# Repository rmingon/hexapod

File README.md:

# Hexapod project

# ON HER LEGS

### Circuit schema with 18 servos connectors.

### PCB View

### 3D View

#### Info
In my hexapod project, i will create a specific pcb with ESP32 for online 
control.

All mcu are connected with I2C bus.

TODO
- [x] Add PCA9685-16 for control servos
- [x] add esp32 
- [x] add MCP9250
- [x] send pcb to JLCPCB
- [x] add lipo 2s charger
- [ ] change esp32 by a k210 kendryte

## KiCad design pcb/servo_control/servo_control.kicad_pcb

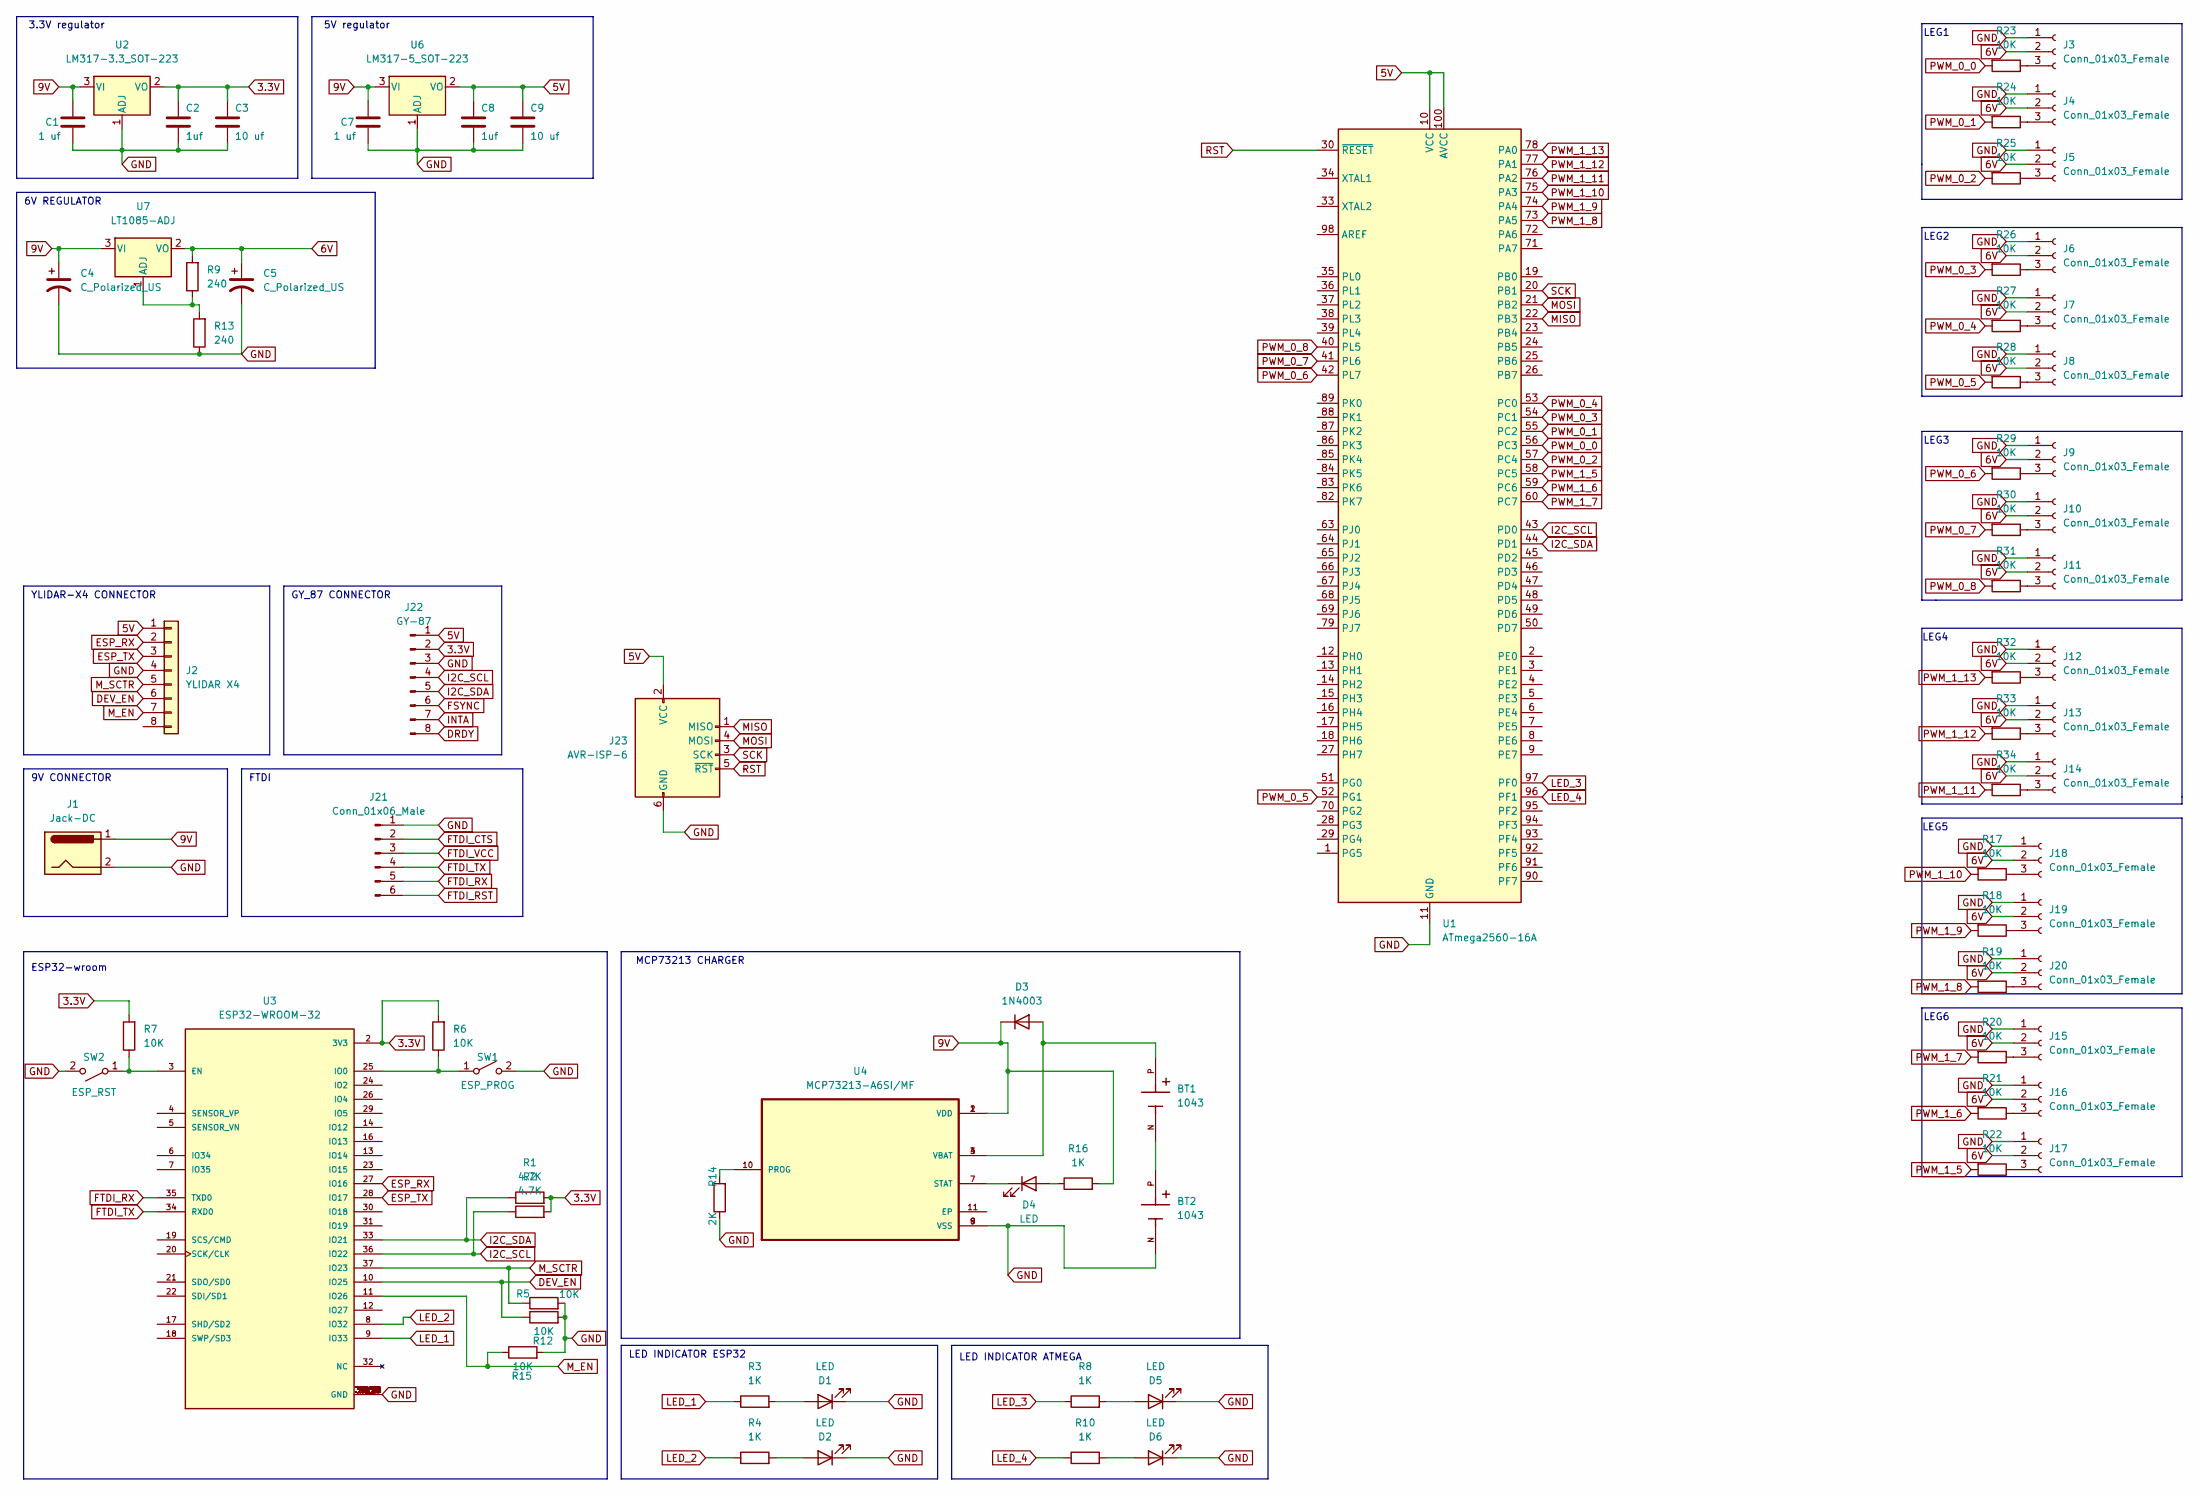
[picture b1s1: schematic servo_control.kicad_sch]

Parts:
BT1, BT2: 1043; BAT_1043; PARTREV H
C1, C7: 1 uf; C_0603_1608Metric
C2, C8: 1uf; C_0603_1608Metric
C3, C9: 10 uf; C_0603_1608Metric
C4, C5: C_Polarized_US; CP_Elec_6.3x3
D1, D2, D4, D5, D6: LED; LED_0603_1608Metric
D3: 1N4003; D_DO-41_SOD81_P10.16mm_Horizontal
J1: Jack-DC; BarrelJack_Horizontal
J2: YLIDAR X4; Hirose_DF13-08P-1.25DSA_1x08_P1.25mm_Vertical
J3, J4, J5, J6, J7, J8, J9, J10, J11, J12, J13, J14, J15, J16, J17, J18, J19, J20: Conn_01x03_Female; PinHeader_1x03_P2.54mm_Vertical
J21: Conn_01x06_Male; PinHeader_1x06_P2.54mm_Vertical
J22: GY-87; PinHeader_1x08_P2.54mm_Vertical
J23: AVR-ISP-6; PinHeader_2x03_P2.54mm_Vertical_SMD
R1, R2: 4.7K; R_0603_1608Metric
R3, R4, R8, R10, R16: 1K; R_0603_1608Metric
R5, R6, R7, R12, R15, R17, R18, R19, R20, R21, R22, R23, R24, R25, R26, R27, R28, R29, R30, R31, R32, R33, R34: 10K; R_0603_1608Metric
R9, R13: 240; R_0603_1608Metric
R14: 2K; R_0603_1608Metric
SW1: ESP_PROG; SW_DIP_SPSTx01_Slide_6.7x4.1mm_W6.73mm_P2.54mm_LowProfile_J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
SW2: ESP_RST; SW_DIP_SPSTx01_Slide_6.7x4.1mm_W6.73mm_P2.54mm_LowProfile_J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
U1: ATmega2560-16A; TQFP-100_14x14mm_P0.5mm
U2: LM317-3.3_SOT-223; SOT-223-3_TabPin2
U3: ESP32-WROOM-32; MODULE_ESP32-WROOM-32; PARTREV 2.9
U4: MCP73213-A6SI/MF; SON50P300X300X100-11N
U6: LM317-5_SOT-223; SOT-223-3_TabPin2
U7: LT1085-ADJ; TO-247-3_Vertical

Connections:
3.3V: C2.1, C3.1, J22.2, R1.2, R2.2, R6.2, R7.2, U2.2 (VO), U3.2 (3V3)
5V: C8.1, C9.1, J2.1, J22.1, J23.2 (VCC), U1.10 (VCC), U1.31 (VCC), U1.61 (VCC), U1.80 (VCC), U1.100 (AVCC), U6.2 (VO)
6V: C5.1, J3.2, J4.2, J5.2, J6.2, J7.2, J8.2, J9.2, J10.2, J11.2, J12.2, J13.2, J14.2, J15.2, J16.2, J17.2, J18.2, J19.2, J20.2, R9.2, U7.2 (VO)
9V: C1.1, C4.1, C7.1, D3.1 (K), J1.1, R16.2, U2.3 (VI), U4.1 (VDD), U4.2 (VDD), U6.3 (VI), U7.3 (VI)
DEV_EN: J2.6, R12.1, U3.10 (IO25)
DRDY: J22.8
ESP_RX: J2.2, U3.27 (IO16)
ESP_TX: J2.3, U3.28 (IO17)
FSYNC: J22.6
FTDI_CTS: J21.2
FTDI_RST: J21.6
FTDI_RX: J21.5, U3.35 (TXD0)
FTDI_TX: J21.4, U3.34 (RXD0)
FTDI_VCC: J21.3
GND: BT2.N, C1.2, C2.2, C3.2, C4.2, C5.2, C7.2, C8.2, C9.2, D1.1 (K), D2.1 (K), D5.1 (K), D6.1 (K), J1.2, J2.4, J3.1, J4.1, J5.1, J6.1, J7.1, J8.1, J9.1, J10.1, J11.1, J12.1, J13.1, J14.1, J15.1, J16.1, J17.1, J18.1, J19.1, J20.1, J21.1, J22.3, J23.6 (GND), R5.2, R12.2, R13.1, R14.1, R15.2, SW1.2 (B), SW2.2 (B), U1.11 (GND), U1.32 (GND), U1.62 (GND), U1.81 (GND), U1.99 (GND), U2.1 (ADJ), U3.1 (GND), U3.15 (GND), U3.38 (GND), U3.39_1 (GND), U3.39_2 (GND), U3.39_3 (GND), U3.39_4 (GND), U3.39_5 (GND), U3.39_6 (GND), U3.39_7 (GND), U3.39_8 (GND), U3.39_9 (GND), U3.39_10 (GND), U3.39_11 (GND), U3.39_12 (GND), U3.39_13 (GND), U3.39_14 (GND), U3.39_15 (GND), U3.39_16 (GND), U3.39_17 (GND), U3.39_18 (GND), U3.39_19 (GND), U3.39_20 (GND), U3.39_21 (GND), U4.8 (VSS), U4.9 (VSS), U6.1 (ADJ)
I2C_SCL: J22.4, R2.1, U1.43 (PD0), U3.36 (IO22)
I2C_SDA: J22.5, R1.1, U1.44 (PD1), U3.33 (IO21)
INTA: J22.7
LED_1: R3.1, U3.9 (IO33)
LED_2: R4.1, U3.8 (IO32)
LED_3: R8.1, U1.97 (PF0)
LED_4: R10.1, U1.96 (PF1)
MISO: J23.1 (MISO), U1.22 (PB3)
MOSI: J23.4 (MOSI), U1.21 (PB2)
M_EN: J2.7, R15.1, U3.11 (IO26)
M_SCTR: J2.5, R5.1, U3.37 (IO23)
unnamed: BT1.N, BT2.P
unnamed: D1.2 (A), R3.2
unnamed: D2.2 (A), R4.2
unnamed: BT1.P, D3.2 (A), U4.3 (VBAT), U4.4 (VBAT)
unnamed: D4.2 (A), R16.1
unnamed: D4.1 (K), U4.7 (STAT)
unnamed: D5.2 (A), R8.2
unnamed: D6.2 (A), R10.2
unnamed: J3.3, R23.1
unnamed: J4.3, R24.1
unnamed: J5.3, R25.1
unnamed: J6.3, R26.1
unnamed: J7.3, R27.1
unnamed: J8.3, R28.1
unnamed: J9.3, R29.1
unnamed: J10.3, R30.1
unnamed: J11.3, R31.1
unnamed: J12.3, R32.1
unnamed: J13.3, R33.1
unnamed: J14.3, R34.1
unnamed: J15.3, R20.1
unnamed: J16.3, R21.1
unnamed: J17.3, R22.1
unnamed: J18.3, R17.1
unnamed: J19.3, R18.1
unnamed: J20.3, R19.1
unnamed: R6.1, SW1.1 (A), U3.25 (IO0)
unnamed: R7.1, SW2.1 (A), U3.3 (EN)
unnamed: R14.2, U4.10 (PROG)
unnamed: R9.1, R13.2, U7.1 (ADJ)
PWM_0_0: R23.2, U1.56 (PC3)
PWM_0_1: R24.2, U1.55 (PC2)
PWM_0_2: R25.2, U1.57 (PC4)
PWM_0_3: R26.2, U1.54 (PC1)
PWM_0_4: R27.2, U1.53 (PC0)
PWM_0_5: R28.2, U1.52 (PG1)
PWM_0_6: R29.2, U1.42 (PL7)
PWM_0_7: R30.2, U1.41 (PL6)
PWM_0_8: R31.2, U1.40 (PL5)
PWM_1_5: R22.2, U1.58 (PC5)
PWM_1_6: R21.2, U1.59 (PC6)
PWM_1_7: R20.2, U1.60 (PC7)
PWM_1_8: R19.2, U1.73 (PA5)
PWM_1_9: R18.2, U1.74 (PA4)
PWM_1_10: R17.2, U1.75 (PA3)
PWM_1_11: R34.2, U1.76 (PA2)
PWM_1_12: R33.2, U1.77 (PA1)
PWM_1_13: R32.2, U1.78 (PA0)
RST: J23.5 (~RST), U1.30 (~RESET)
SCK: J23.3 (SCK), U1.20 (PB1)

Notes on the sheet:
5V regulator
3.3V regulator
LEG5
YLIDAR-X4 CONNECTOR
LEG4
LED INDICATOR ATMEGA
GY_87 CONNECTOR
MCP73213 CHARGER
LEG6
ESP32-wroom
6V REGULATOR
LEG3
LEG2
LED INDICATOR ESP32
LEG1
9V CONNECTOR
FTDI

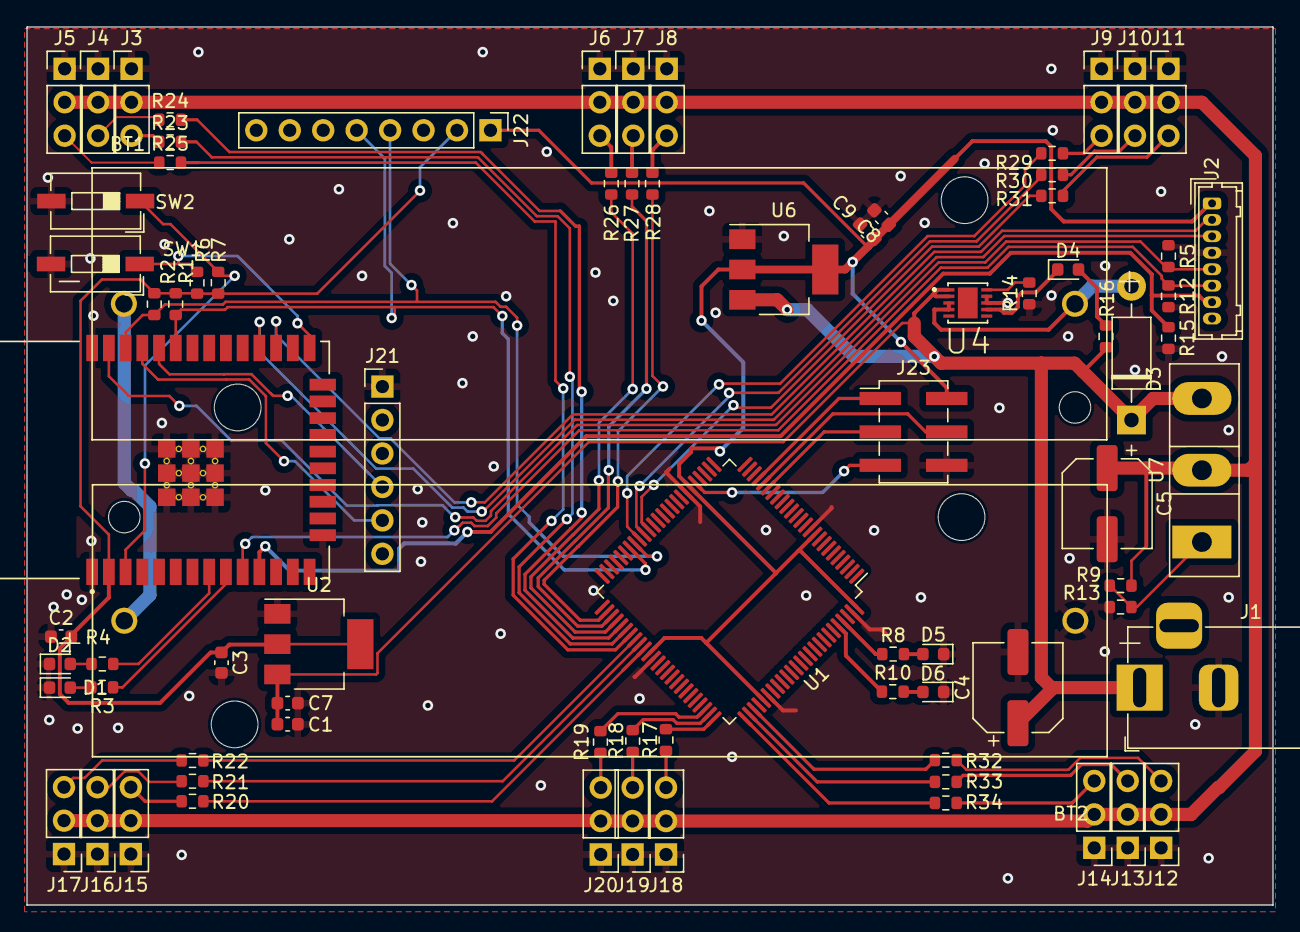
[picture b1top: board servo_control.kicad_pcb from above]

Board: 2 copper layers, 94.6 x 66.7 mm, 80 parts (0 on the bottom side), 70 nets.

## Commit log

2023-01-05 add pcb
2023-01-07 add legs connector
2023-01-08 all legs + add esp32 wroom on pcb
2023-01-08 add lib ESP32-WROOM-32
2023-01-08 add ftdi
2023-01-08 add i2c
2023-01-09 add track vcc servo
2023-01-09 schema picture
2023-01-10 add gnd zone
2023-01-10 add picture + edit readme
2023-01-14 change atmega2560 to PCA9685
2023-01-14 wiring pcb for PCA9685
2023-01-14 finish pcb
2023-01-14 update picture
2023-01-14 add plot
2023-01-14 up readme
2023-01-25 first commit code
2023-01-25 change builder
2023-01-26 add main
2023-01-26 add gitignore
2023-01-26 fix servo header
2023-01-31 edit project name
2023-01-31 add 5V regulator
2023-01-31 add jack
2023-02-01 add servo datasheet
2023-02-01 add dual cell charger
2023-02-01 add lipo 2S charger
2023-02-02 add 18650 support + LT1085 regulator
2023-02-03 add 6V regulator
2023-02-03 update view
2023-02-03 add MCP73213
2023-02-18 fix PCA9685 footprint
2023-02-18 add 2s lipo charger
2023-03-04 fix gnd 5v + adjust 6V
2023-03-12 update mcp9586 for i2c address
2023-03-23 add lidar lib
2023-03-23 deleted
2023-03-23 add lidar pin
2023-03-23 first launch
2023-03-23 add servo lib
2023-03-23 add led lib
2023-03-23 global gitignore
2023-03-23 lidar class
2023-03-25 add lidar method
2023-03-25 add lidar test
2023-03-25 add serial speed
2023-03-25 set servo class
2023-03-25 servo to class
2023-03-25 remove conf from git
2023-03-25 add udp
2023-03-25 async udp
2023-03-25 add servo method
2023-03-25 add readme
2023-04-02 add resistor current
2023-04-03 move lidar wiring
2023-04-03 move pcf
2023-04-04 rewire
2023-08-25 pass servo control to atmega2560
2023-08-25 add pcb atmega2560
2023-08-28 add spi atmega2560
2023-08-28 add led atmega2560
2023-08-28 add atmega2560 servos wiring
2023-09-07 rewiring
2023-09-11 remove idea + vscode
2023-09-12 first code
2023-09-14 set atmega to 5v
2023-09-14 add picture with first legs support
2023-09-15 change servo wiring
2023-09-15 change gnd mass
2023-09-15 change esp32 vias
